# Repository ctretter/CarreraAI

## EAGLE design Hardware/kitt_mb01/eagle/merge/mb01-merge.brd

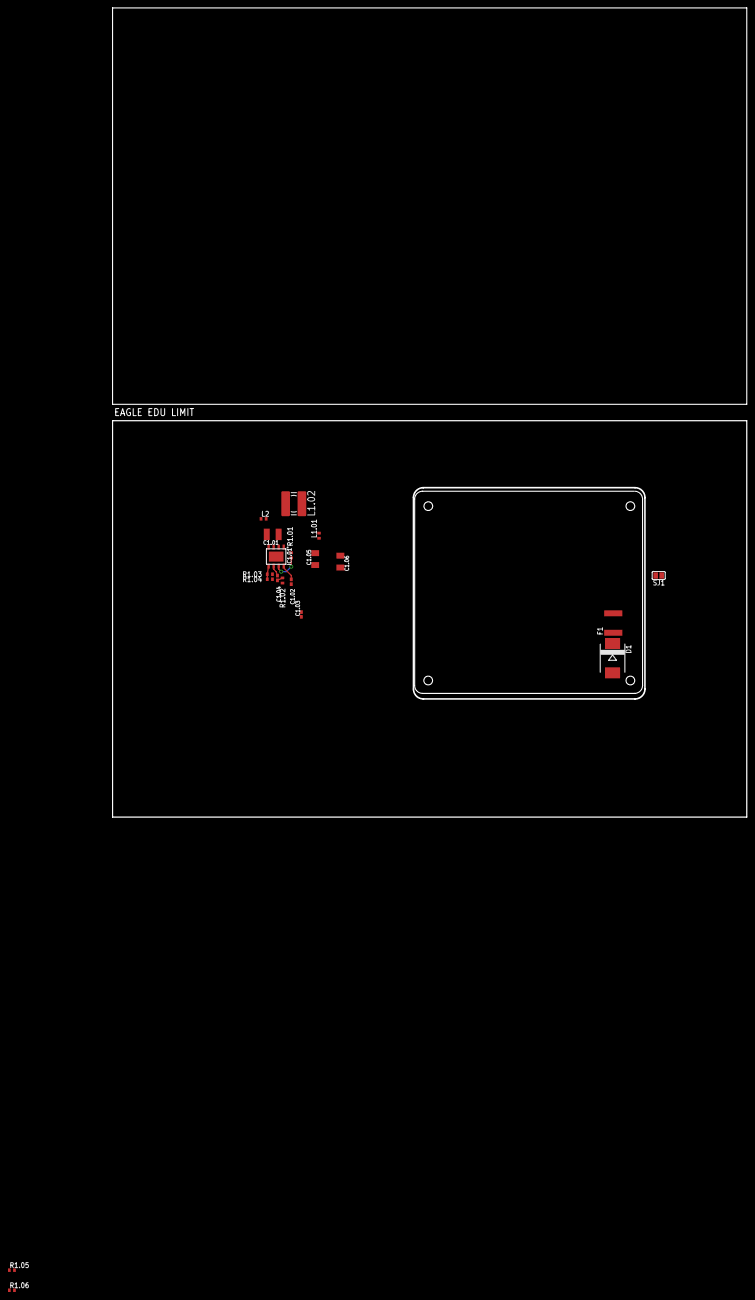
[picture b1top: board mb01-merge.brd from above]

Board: 2 copper layers, 160.0 x 100.0 mm, 21 parts (0 on the bottom side), 14 nets.

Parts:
C1.01: 22uF/25V; C1210K
C1.02, C1.03: 100nF; C0402K
C1.04: XX; C0402K
C1.05, C1.06: 22uF/6.3V; C1206K
D1: MBRS320T3; SMC
F1: 750mA; MF-SMDF050
IC1.01: RT8293A; SOIC-8-PAD
L1.01, L2: BEAD; 0402
L1.02: 4.7uH; POWER-CHOKE_WE-TPC
R1.01: 100kR; R0402
R1.02, R1.03, R1.04: XX; R0402
R1.05, R1.06: [0R]; R0402
SJ1: SJ
U$1: REF_GCB2_BS
U$2: REF_GCB2_TS

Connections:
+5V: R1.05.1, R1.06.2
+12V: D1.C, F1.1
GND: C1.01.2, C1.02.2, C1.05.2, C1.06.2, IC1.01.4, IC1.01.PAD, R1.02.1, R1.04.1, SJ1.2
unnamed: F1.2, L1.01.1
unnamed: C1.01.1, IC1.01.2, L1.01.2, R1.01.1
unnamed: IC1.01.7, R1.01.2
unnamed: C1.02.1, IC1.01.8
unnamed: C1.04.2, R1.02.2
unnamed: C1.04.1, IC1.01.6
unnamed: IC1.01.5, R1.03.1, R1.04.2
unnamed: C1.05.1, C1.06.1, L1.02.1, L2.1, R1.03.2
unnamed: C1.03.2, IC1.01.3, L1.02.2
unnamed: C1.03.1, IC1.01.1
unnamed: L2.2, R1.05.2, R1.06.1

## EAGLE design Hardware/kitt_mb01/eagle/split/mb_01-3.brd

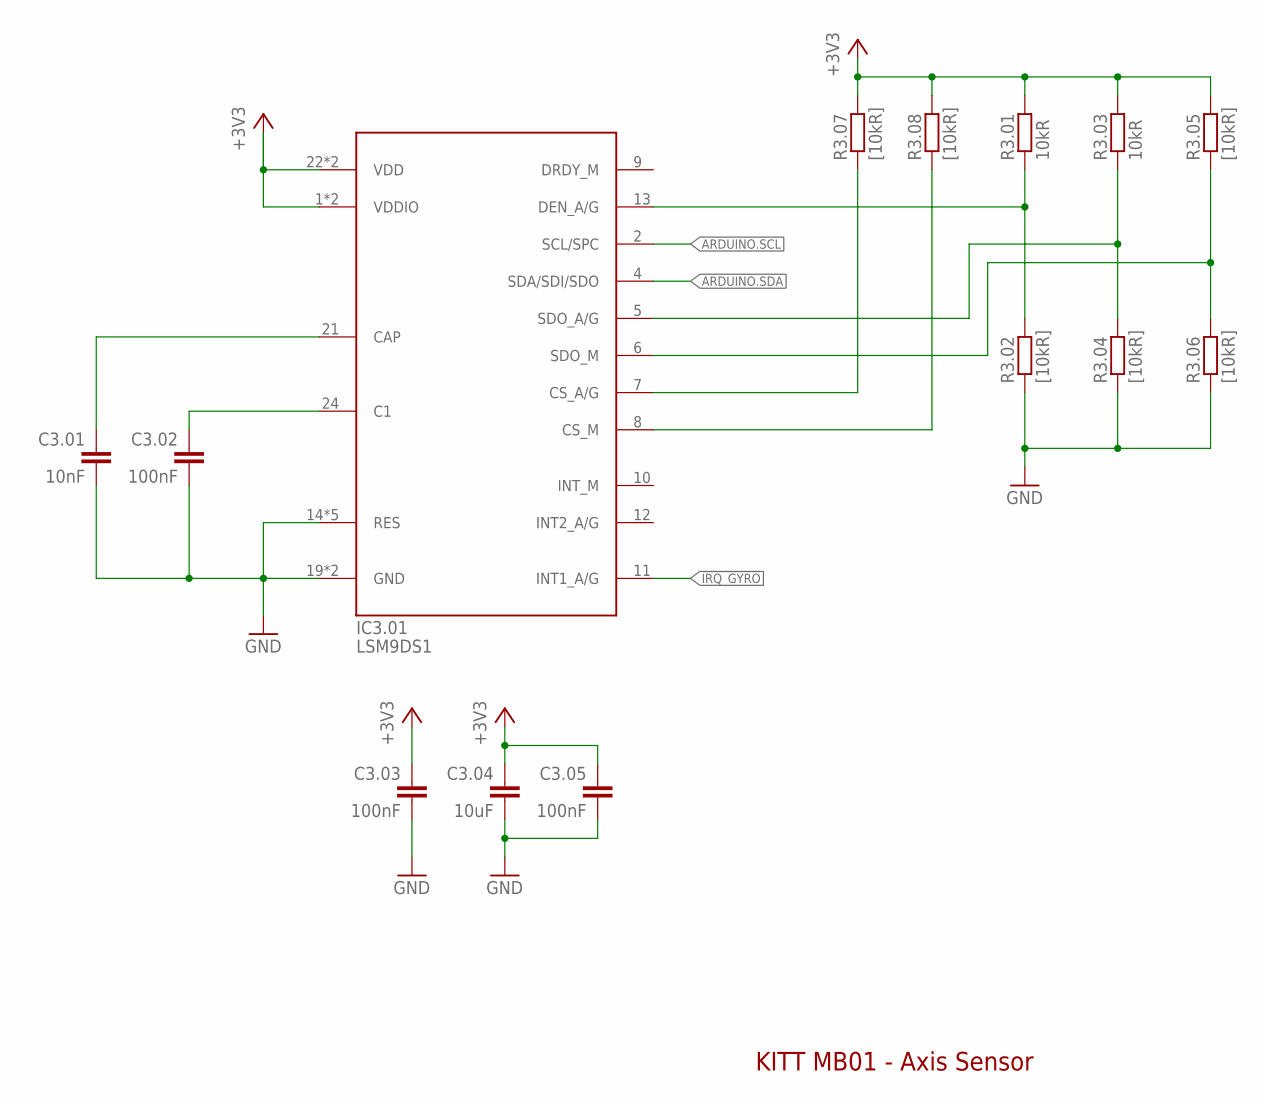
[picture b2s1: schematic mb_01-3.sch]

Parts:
C3.01: 10nF; C0402
C3.02, C3.03, C3.05: 100nF; C0402
C3.04: 10uF; C0603K
IC3.01: LSM9DS1; LGA-24
R3.01, R3.03: 10kR; R0402
R3.02, R3.04, R3.05, R3.06, R3.07, R3.08: [10kR]; R0402

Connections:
!IRQ_GYRO: IC3.01.11 (INT1_A/G)
+3V3: C3.03.1, C3.04.1, C3.05.1, IC3.01.1 (VDDIO), IC3.01.3 (VDDIO), IC3.01.22 (VDD), IC3.01.23 (VDD), R3.01.2, R3.03.2, R3.05.2, R3.07.2, R3.08.2
GND: C3.01.2, C3.02.2, C3.03.2, C3.04.2, C3.05.2, IC3.01.14 (RES), IC3.01.15 (RES), IC3.01.16 (RES), IC3.01.17 (RES), IC3.01.18 (RES), IC3.01.19 (GND), IC3.01.20 (GND), R3.02.1, R3.04.1, R3.06.1
unnamed: C3.01.1, IC3.01.21 (CAP)
unnamed: C3.02.1, IC3.01.24 (C1)
unnamed: IC3.01.13 (DEN_A/G), R3.01.1, R3.02.2
unnamed: IC3.01.5 (SDO_A/G), R3.03.1, R3.04.2
unnamed: IC3.01.7 (CS_A/G), R3.07.1
unnamed: IC3.01.6 (SDO_M), R3.05.1, R3.06.2
unnamed: IC3.01.8 (CS_M), R3.08.1

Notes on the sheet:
KITT MB01 - Axis Sensor

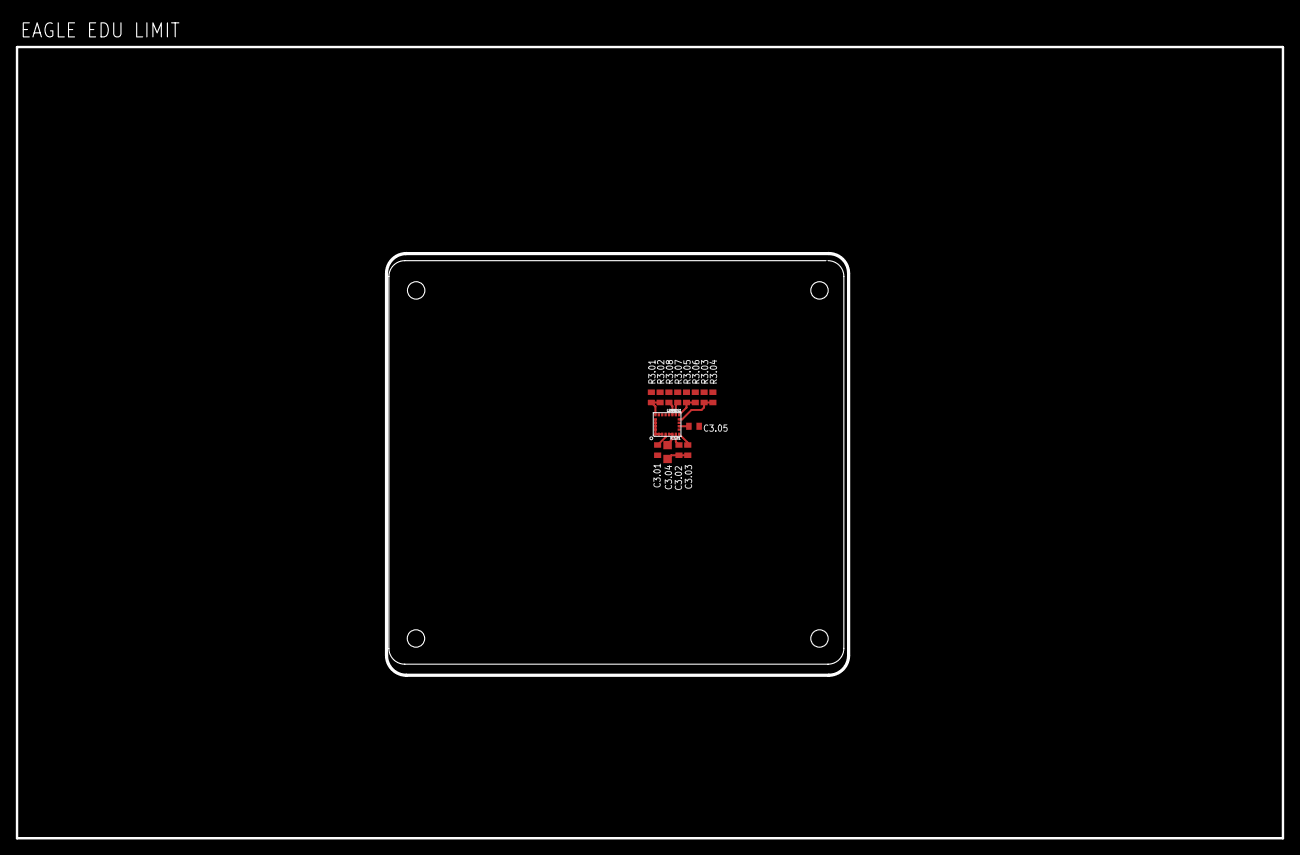
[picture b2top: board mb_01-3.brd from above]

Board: 8 copper layers, 160.0 x 100.0 mm, 15 parts (0 on the bottom side), 9 nets.

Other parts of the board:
U$1: REF_GCB2_TS

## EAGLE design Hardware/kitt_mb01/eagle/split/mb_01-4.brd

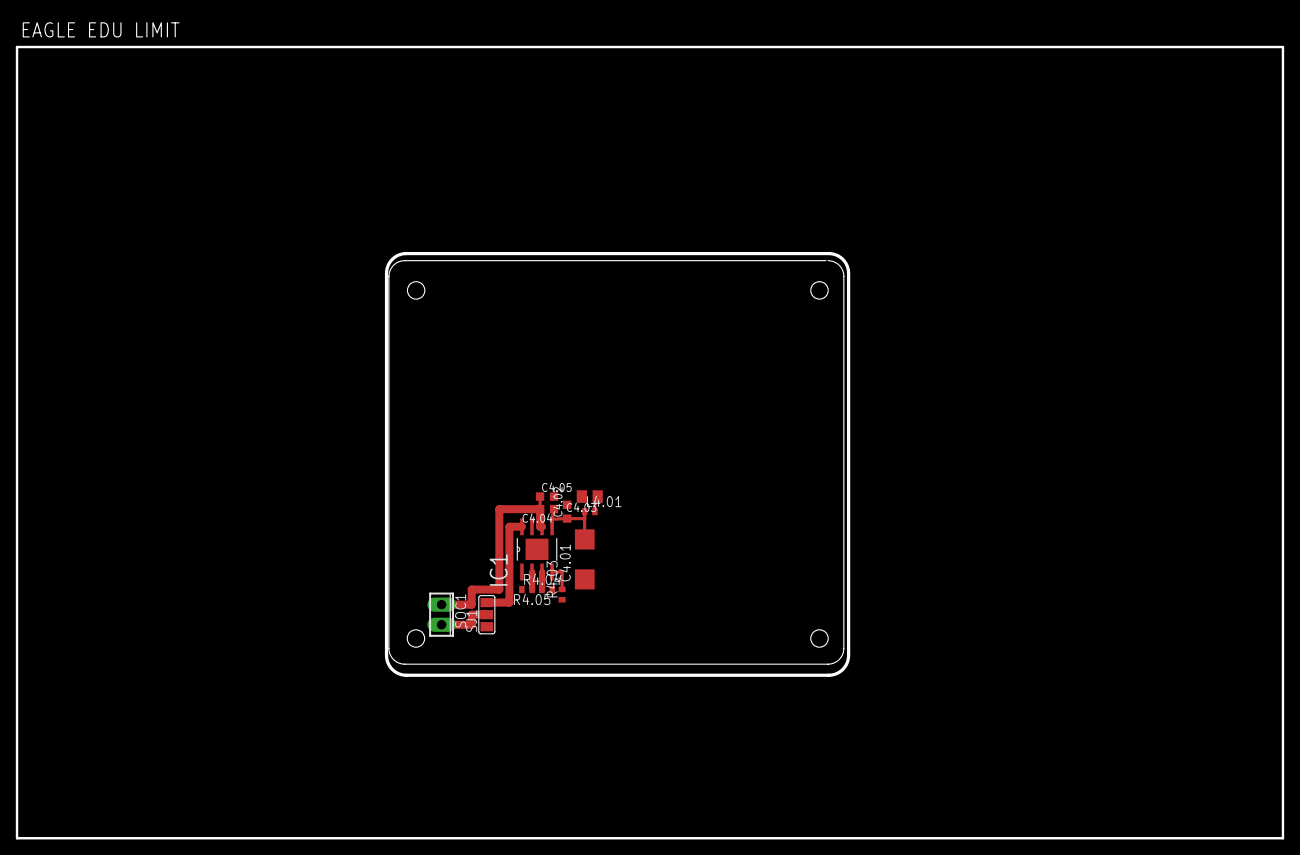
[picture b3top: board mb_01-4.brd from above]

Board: 8 copper layers, 160.0 x 100.0 mm, 13 parts (0 on the bottom side), 9 nets.

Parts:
C4.01: 47uF/25V; C/6032-28R
C4.02: 100nF/25V; C0603K
C4.03: C0805K
C4.04, C4.05: 220nF/25V; C0603K
IC1: HSOP8
L4.01: BEAD; 0402
R4.03: 22kR; R0402
R4.04, R4.05: 1kR; R0402
SJ1: SJ_2
SOC1: 2POL254
U$1: REF_GCB2_TS

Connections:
+12V: C4.03.1, L4.01.2
GND: C4.01.-, C4.02.2, C4.03.2, C4.05.2, IC1.1, IC1.7, IC1.THERMAL, R4.03.1, R4.04.1, R4.05.1, SJ1.1
MOT.IN1: IC1.3, R4.05.2
MOT.IN2: IC1.2, R4.04.2
unnamed: SJ1.2, SOC1.2
unnamed: C4.01.+, C4.02.1, C4.04.1, IC1.5, L4.01.1
unnamed: C4.04.2, C4.05.1, IC1.6, SOC1.1
unnamed: IC1.8, SJ1.3
unnamed: IC1.4, R4.03.2

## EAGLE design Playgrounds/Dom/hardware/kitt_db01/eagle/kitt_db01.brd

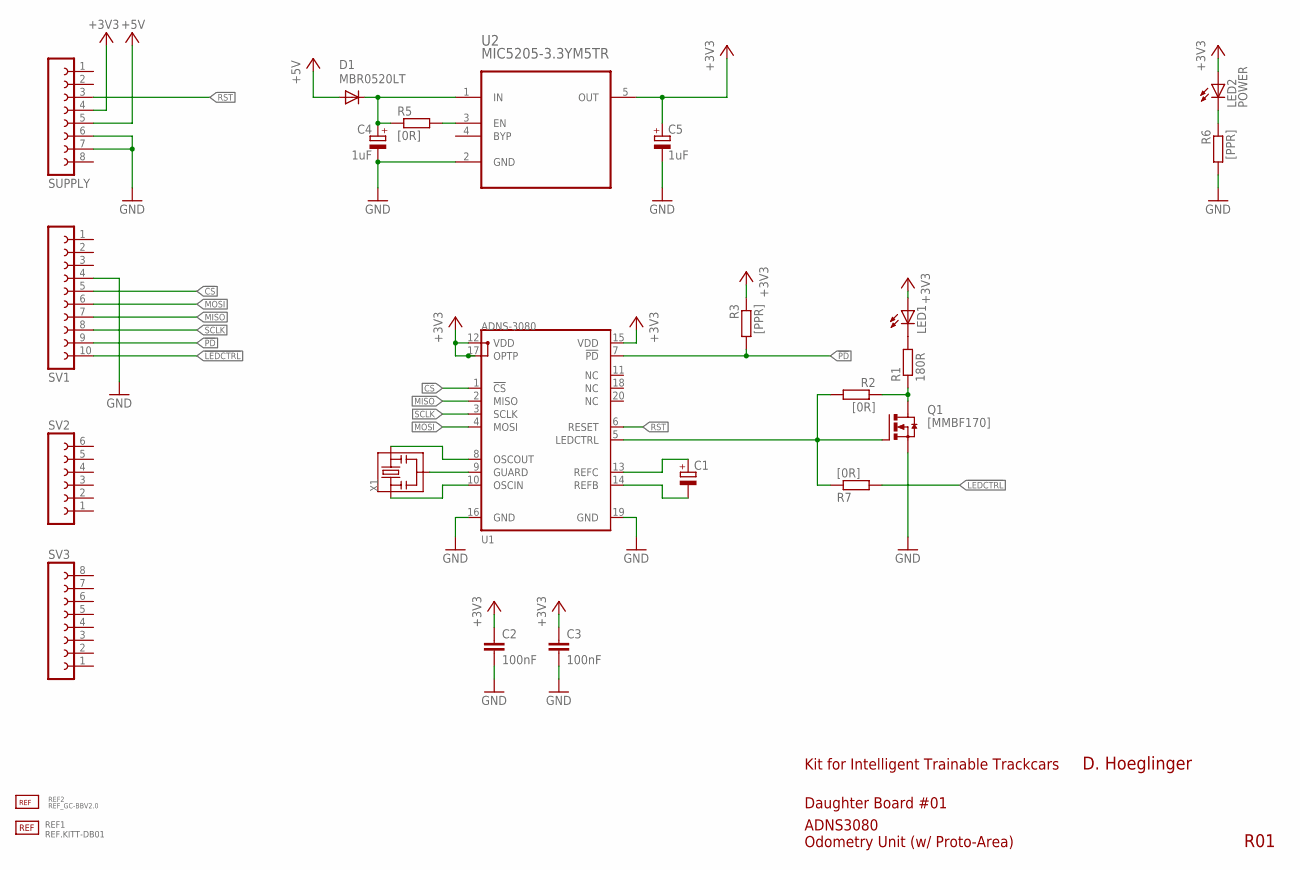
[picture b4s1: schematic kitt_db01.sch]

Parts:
C1: CPOL-EUSMCB; SMC_B
C2, C3: 100nF; C0805K
C4, C5: 1uF; A/3216-18W
D1: MBR0520LT; SOD123
LED1: LED5MM
LED2: POWER; CHIP-LED0805
Q1: [MMBF170]; SOT223
R1: 180R; R0805
R2, R5, R7: [0R]; R0805
R3, R6: [PPR]; R0805
REF1: REF.KITT-DB01; REF_KITT-DB01
REF2: REF_GC-BBV2.0; REF_GHOSTCAR
SUPPLY: FE08-1; FE08
SV1: FE10-1; FE10
SV2: FE06-1; FE06
SV3: FE08-1; FE08
U1: ADNS-3080
U2: MIC5205-3.3YM5TR; SOT95P280X130-5N
X1: RESON; RESON-SMD

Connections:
!CS: SV1.5, U1.1 (!CS)
!LEDCTRL: R7.2, SV1.10
!PD: R3.2, SV1.9, U1.7 (!PD)
+3V3: C2.1, C3.1, C5.+, LED1.A, LED2.A, R3.1, SUPPLY.4, U1.12 (VDD), U1.15 (VDD), U1.17 (OPTP), U2.5 (OUT)
+5V: D1.A, SUPPLY.5
GND: C2.2, C3.2, C4.-, C5.-, Q1.3 (S), R6.2, SUPPLY.6, SUPPLY.7, SV1.4, U1.16 (GND), U1.19 (GND), U2.2 (GND)
MISO: SV1.7, U1.2 (MISO)
MOSI: SV1.6, U1.4 (MOSI)
unnamed: U1.9 (GUARD), X1.2
unnamed: U1.8 (OSCOUT), X1.3
unnamed: U1.10 (OSCIN), X1.1
unnamed: Q1.1 (G), R2.2, R7.1, U1.5 (LEDCTRL)
unnamed: C1.+, U1.13 (REFC)
unnamed: C1.-, U1.14 (REFB)
unnamed: Q1.2 (D), Q1.4 (D), R1.1, R2.1
unnamed: LED1.K (C), R1.2
unnamed: C4.+, D1.C, R5.1, U2.1 (IN)
unnamed: R5.2, U2.3 (EN)
unnamed: LED2.C, R6.1
RST: SUPPLY.3, U1.6 (RESET)
SCLK: SV1.8, U1.3 (SCLK)

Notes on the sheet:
Kit for Intelligent Trainable Trackcars
Daughter Board #01
ADNS3080 Odometry Unit (w/ Proto-Area)
R01
D. Hoeglinger

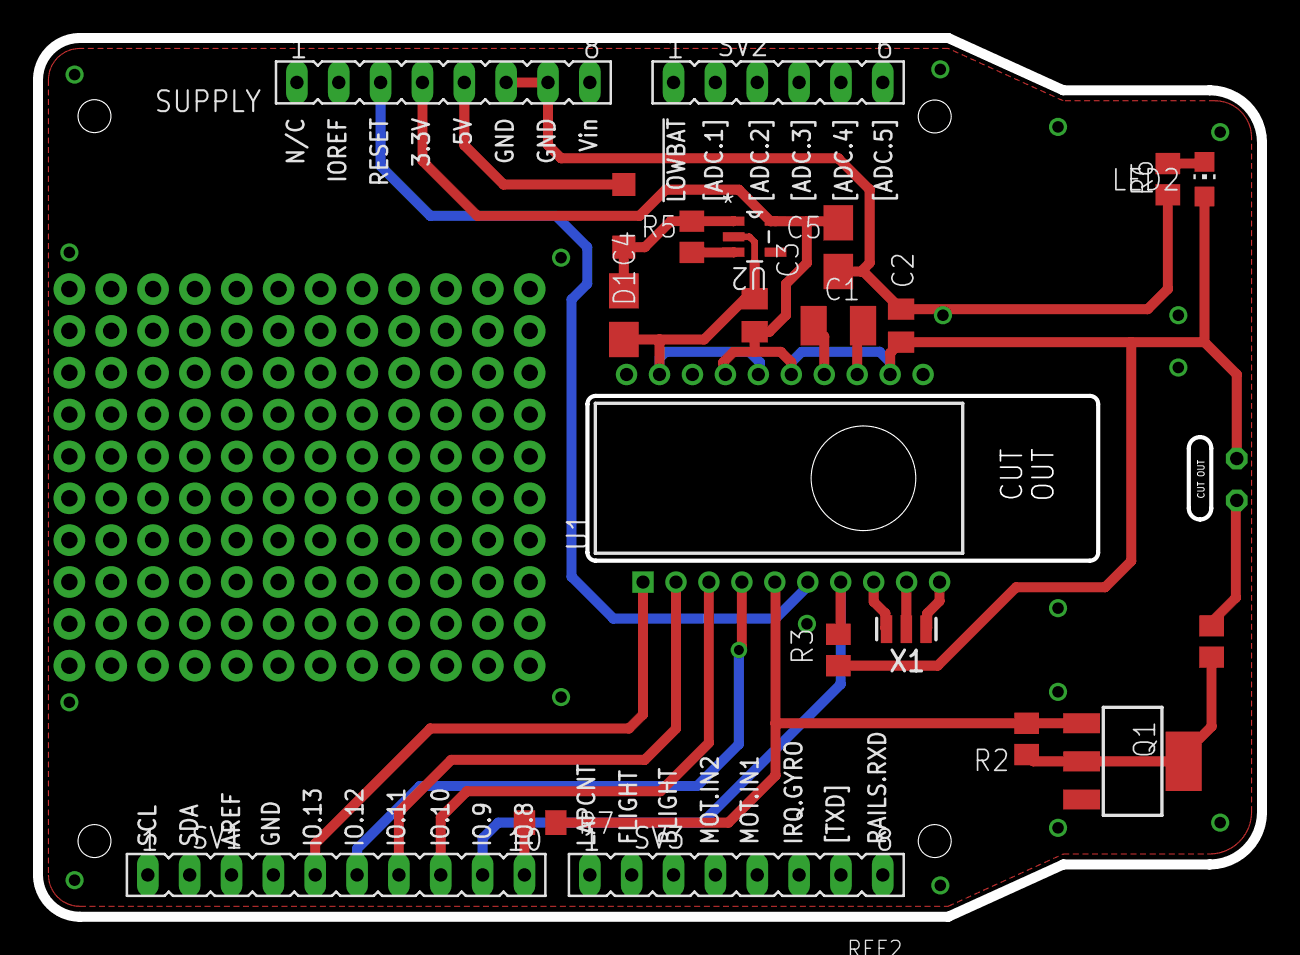
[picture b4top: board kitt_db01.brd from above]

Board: 2 copper layers, 74.3 x 53.3 mm, 25 parts (1 on the bottom side), 21 nets.

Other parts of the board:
U$1: A3L-LOC

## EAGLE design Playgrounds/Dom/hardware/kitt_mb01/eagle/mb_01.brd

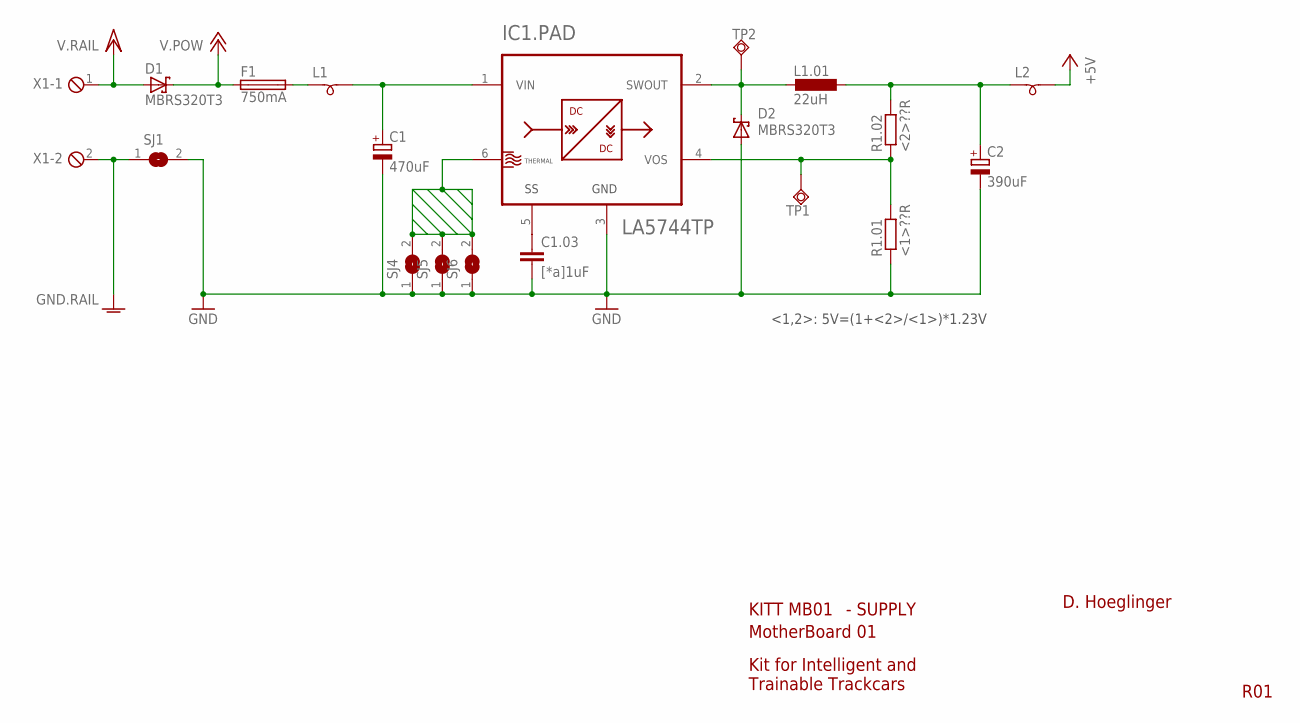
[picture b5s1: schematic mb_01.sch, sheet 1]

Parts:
C1: 470uF; SMC_P
C1.03: [*a]1uF; C0805K
C2: 390uF; SMC_P
D1, D2: MBRS320T3; SMC
F1: 750mA; MF-SMDF050
IC1: LA5744TP; TP-HPA
L1, L2: SM-B5
L1.01: 22uH; POWER-CHOKE_WE-TPC
R1.01: <1>??R; R0805
R1.02: <2>??R; R0805
SJ1, SJ4, SJ5, SJ6: SJ
TP1, TP2: TPSQTP19SQ; TP19SQ
X1: MPT2; 2POL254

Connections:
+5V: L2.2
+12V: D1.C, F1.1
GND: C1.-, C1.03.2, C2.-, D2.A, IC1.3 (GND), R1.01.1, SJ1.2, SJ4.1, SJ5.1, SJ6.1; also elsewhere on the board
GNDA: SJ1.1, X1.2
unnamed: C1.03.1, IC1.5 (SS)
unnamed: F1.2, L1.1
unnamed: C1.+, IC1.1 (VIN), L1.2
unnamed: IC1.4 (VOS), R1.01.2, R1.02.1, TP1.TP
unnamed: D2.C, IC1.2 (SWOUT), L1.01.2, TP2.TP
unnamed: C2.+, L1.01.1, L2.1, R1.02.2
THERM.1: IC1.6 (THERMAL), SJ4.2, SJ5.2, SJ6.2
VCC/2: D1.A, X1.1; also elsewhere on the board

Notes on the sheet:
<1,2>: 5V=(1+<2>/<1>)*1.23V
KITT MB01
Kit for Intelligent and Trainable Trackcars
MotherBoard 01
- SUPPLY
D. Hoeglinger
R01

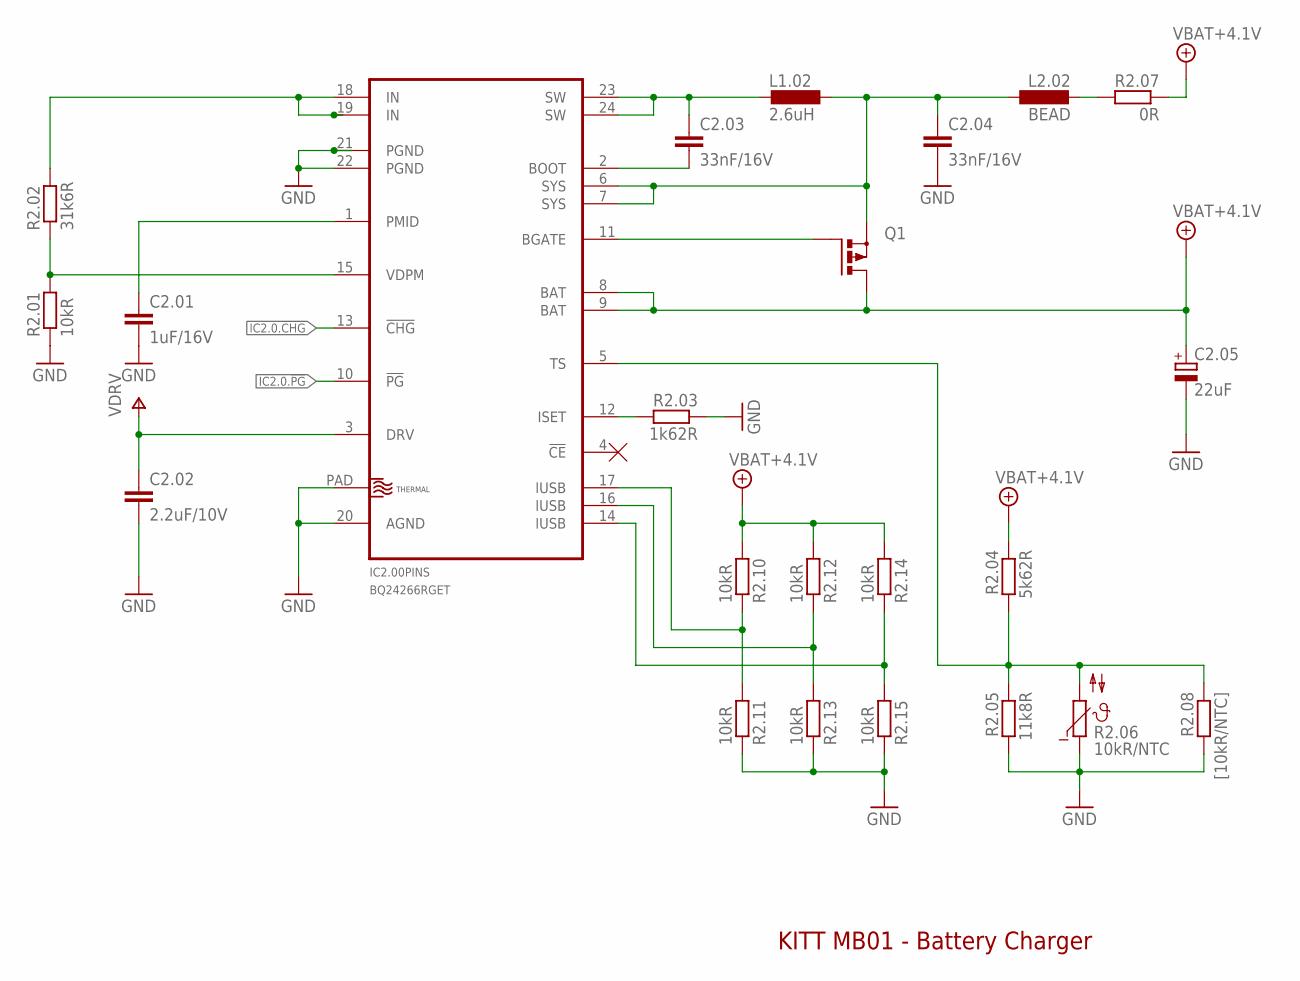
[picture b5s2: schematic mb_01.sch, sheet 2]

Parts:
C2.01: 1uF/16V; C0805
C2.02: 2.2uF/10V; C0805
C2.03: 33nF/16V; C0603
C2.04: 33nF/16V; C0805
C2.05: 22uF; A/3216-18R
IC2.00: BQ24266RGET; VQFN-24
L1.02: 2.6uH; POWER-CHOKE_WE-TPC
L2.02: BEAD; L2012C
Q1: P-MOSFET-SO8; SO-08
R2.01, R2.10, R2.11, R2.12, R2.13, R2.14, R2.15: 10kR; R0402
R2.02: 31k6R; R0402
R2.03: 1k62R; R0402
R2.04: 5k62R; R0402
R2.05: 11k8R; R0402
R2.06: 10kR/NTC; P642
R2.07: 0R; R0402
R2.08: [10kR/NTC]; R0402

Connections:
+4.1V: C2.05.+, IC2.00.8 (BAT), IC2.00.9 (BAT), Q1.5 (D), Q1.6 (D), Q1.7 (D), Q1.8 (D), R2.04.1, R2.07.1, R2.10.2, R2.12.2, R2.14.2
GND: C2.01.2, C2.02.2, C2.04.2, C2.05.-, IC2.00.20 (AGND), IC2.00.21 (PGND), IC2.00.22 (PGND), IC2.00.PAD (THERMAL), R2.01.1, R2.03.1, R2.05.2, R2.06.1, R2.08.2, R2.11.1, R2.13.1, R2.15.1; also elsewhere on the board
IC2.0.!CHG: IC2.00.13 (!CHG)
IC2.0.!PG: IC2.00.10 (!PG)
unnamed: C2.01.1, IC2.00.1 (PMID)
unnamed: IC2.00.18 (IN), IC2.00.19 (IN), R2.02.2
unnamed: IC2.00.15 (VDPM), R2.01.2, R2.02.1
unnamed: C2.03.1, IC2.00.23 (SW), IC2.00.24 (SW), L1.02.2
unnamed: C2.03.2, IC2.00.2 (BOOT)
unnamed: IC2.00.11 (BGATE), Q1.4 (G)
unnamed: IC2.00.5 (TS), R2.04.2, R2.05.1, R2.06.2, R2.08.1
unnamed: L2.02.2, R2.07.2
unnamed: C2.04.1, IC2.00.6 (SYS), IC2.00.7 (SYS), L1.02.1, L2.02.1, Q1.1 (S), Q1.2 (S), Q1.3 (S)
unnamed: IC2.00.12 (ISET), R2.03.2
unnamed: IC2.00.17 (IUSB), R2.10.1, R2.11.2
unnamed: IC2.00.16 (IUSB), R2.12.1, R2.13.2
unnamed: IC2.00.14 (IUSB), R2.14.1, R2.15.2
V+: C2.02.1, IC2.00.3 (DRV)

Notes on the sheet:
KITT MB01 - Battery Charger

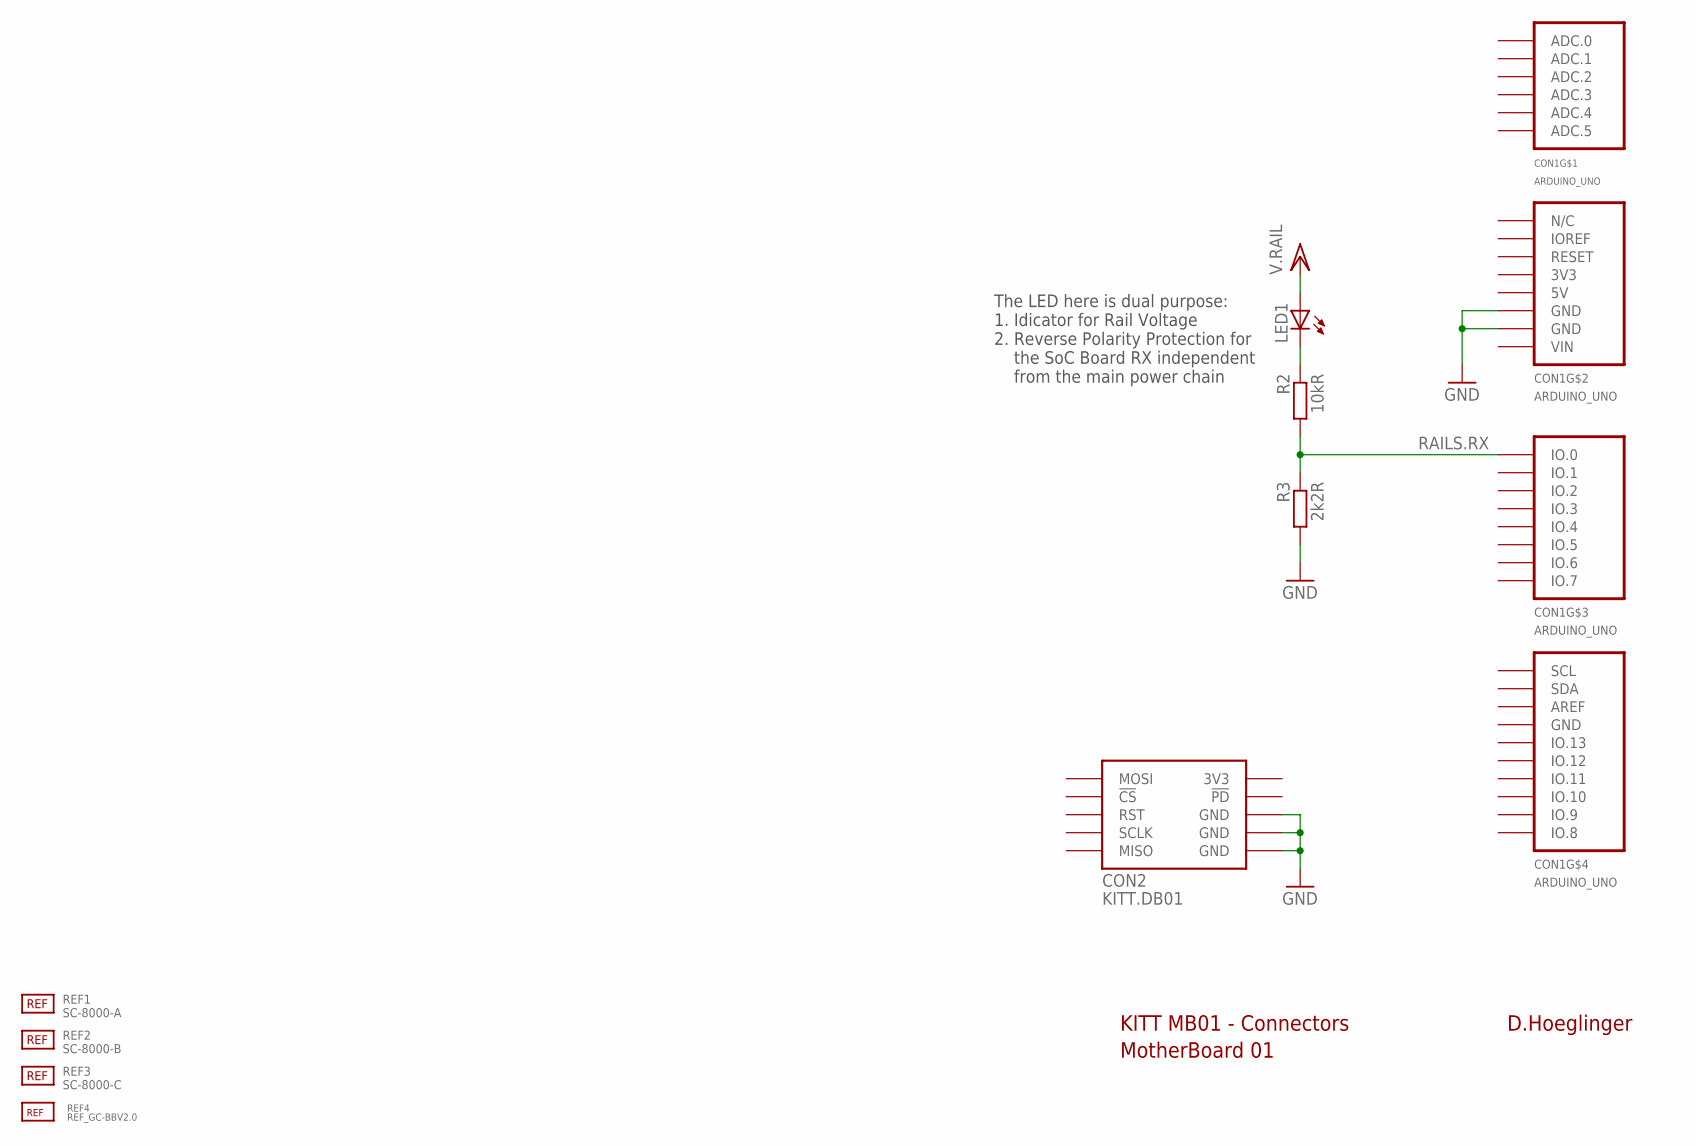
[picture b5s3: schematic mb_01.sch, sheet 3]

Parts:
CON1: ARDUINO_UNO; AU_PINS
CON2: KITT.DB01; KITT_DB01
LED1: LG_T679-E1F1-1; PLCC2
R2: 10kR; M0805
R3: 2k2R; M0805
REF1: SC-8000-A
REF2: SC-8000-B
REF3: SC-8000-C
REF4: REF_GC-BBV2.0; REF_GHOSTCAR

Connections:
GND: CON1.GND2 (GND), CON1.GND3 (GND), CON2.6 (GND), CON2.8 (GND), CON2.10 (GND), R3.2; also elsewhere on the board
unnamed: LED1.C, R2.1
RAILS.RX: CON1.IO.0, R2.2, R3.1
VCC/2: LED1.A; also elsewhere on the board

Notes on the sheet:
The LED here is dual purpose: 1. Idicator for Rail Voltage 2. Reverse Polarity Protection for the SoC Board RX independent from the main power chain
D.Hoeglinger
KITT MB01 - Connectors
MotherBoard 01

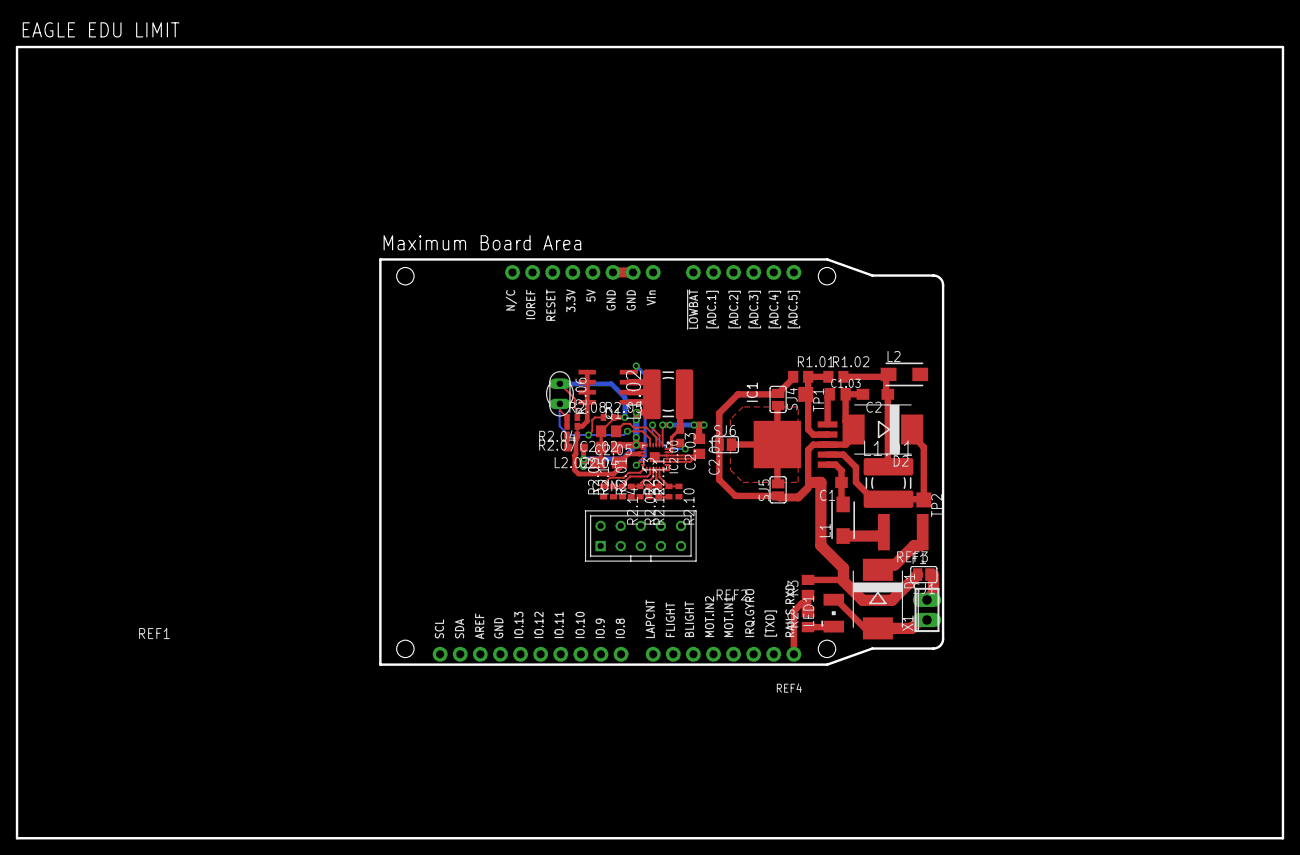
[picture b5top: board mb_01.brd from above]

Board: 2 copper layers, 160.0 x 100.0 mm, 51 parts (1 on the bottom side), 28 nets.
